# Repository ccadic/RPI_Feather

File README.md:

# RPI_Feather
Raspberry to Feather connector

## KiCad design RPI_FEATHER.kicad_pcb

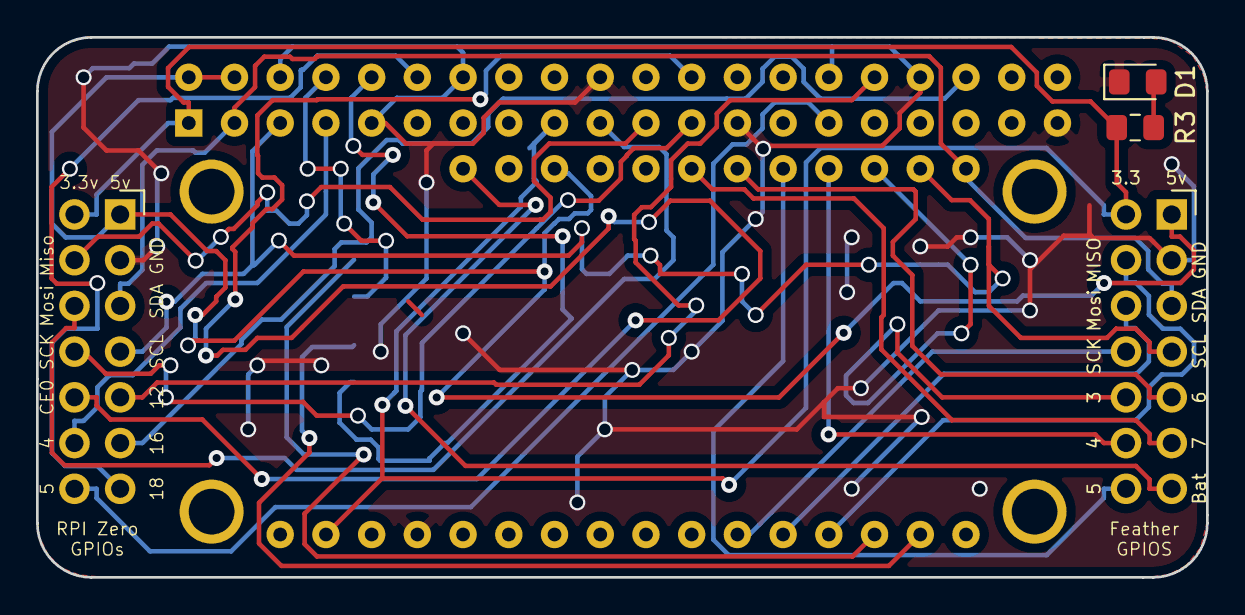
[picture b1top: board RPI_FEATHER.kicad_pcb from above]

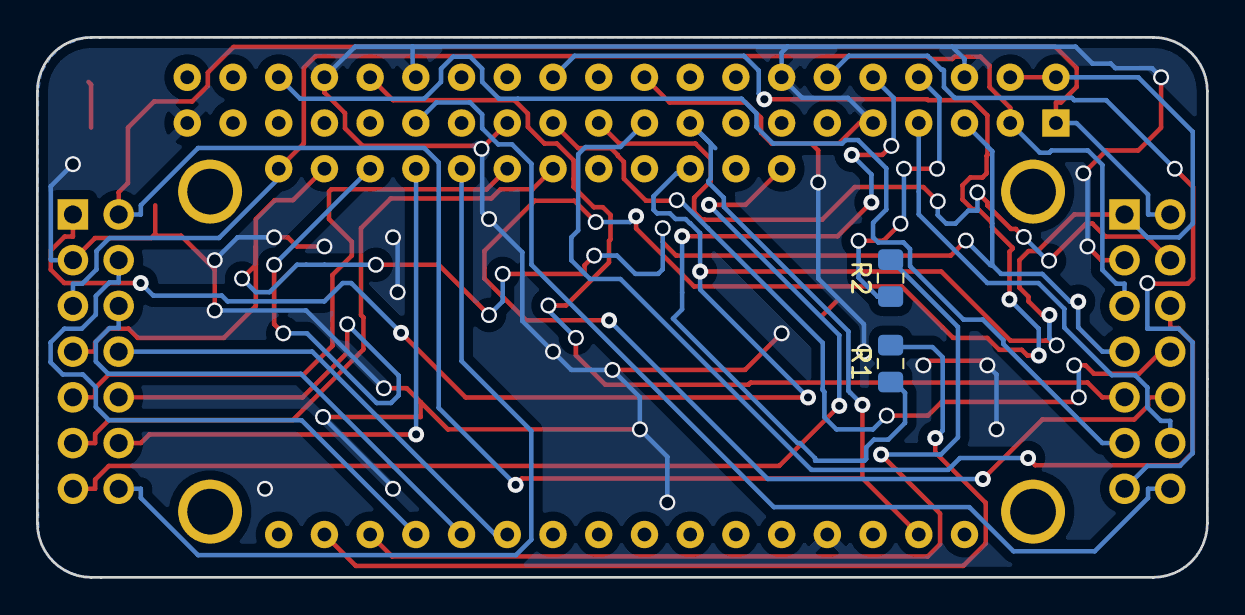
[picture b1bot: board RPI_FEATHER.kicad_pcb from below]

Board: 2 copper layers, 65.0 x 30.0 mm, 8 parts (2 on the bottom side), 28 nets.

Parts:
D1: LED_Small; LED_0805_2012Metric_Pad1.15x1.40mm_HandSolder
J1: FeathCon; PinSocket_2x07_P2.54mm_Vertical
J2: RpiCon; PinSocket_2x07_P2.54mm_Vertical
PI1: BPLUS_GPIO; PHAT
R1, R2: 22R; R_0805_2012Metric_Pad1.15x1.40mm_HandSolder
R3: 330; R_0805_2012Metric_Pad1.15x1.40mm_HandSolder
U1: FeatherFP; PCB_FeatherWing

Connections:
3.3v: J1.2, J2.2, PI1.1, PI1.17, R3.1, U1.27
/3: J1.10, U1.3
/4: J1.12, U1.4
/5: J1.14, U1.5
/5v: J1.1, J2.1, PI1.2, PI1.4, U1.10
/6: J1.9, U1.6
/7: J1.11, U1.7
/BAT: J1.13, U1.12
/MISO: J1.4, U1.16
/MOSI: J1.6, U1.17
/RX: PI1.8, R2.1
/SCK: J1.8, U1.18
/TX: PI1.10, R1.1
GND: D1.1, J1.3, J2.3, PI1.6, PI1.9, PI1.14, PI1.20, PI1.25, PI1.30, PI1.34, PI1.39, U1.25
Gpio4: J2.12, PI1.7
Gpio5: J2.14, PI1.29
Gpio12: J2.9, PI1.32
Gpio16: J2.11, PI1.36
Gpio18: J2.13, PI1.12
unnamed: D1.2, R3.2
unnamed: R1.2, U1.14
unnamed: R2.2, U1.15
SCL: J1.7, J2.7, PI1.5, U1.2
SDA: J1.5, J2.5, PI1.3, U1.1
SPI_CE0: J2.10, PI1.24
SPI_MISO: J2.4, PI1.21
SPI_MOSI: J2.6, PI1.19
SPI_SCK: J2.8, PI1.23
